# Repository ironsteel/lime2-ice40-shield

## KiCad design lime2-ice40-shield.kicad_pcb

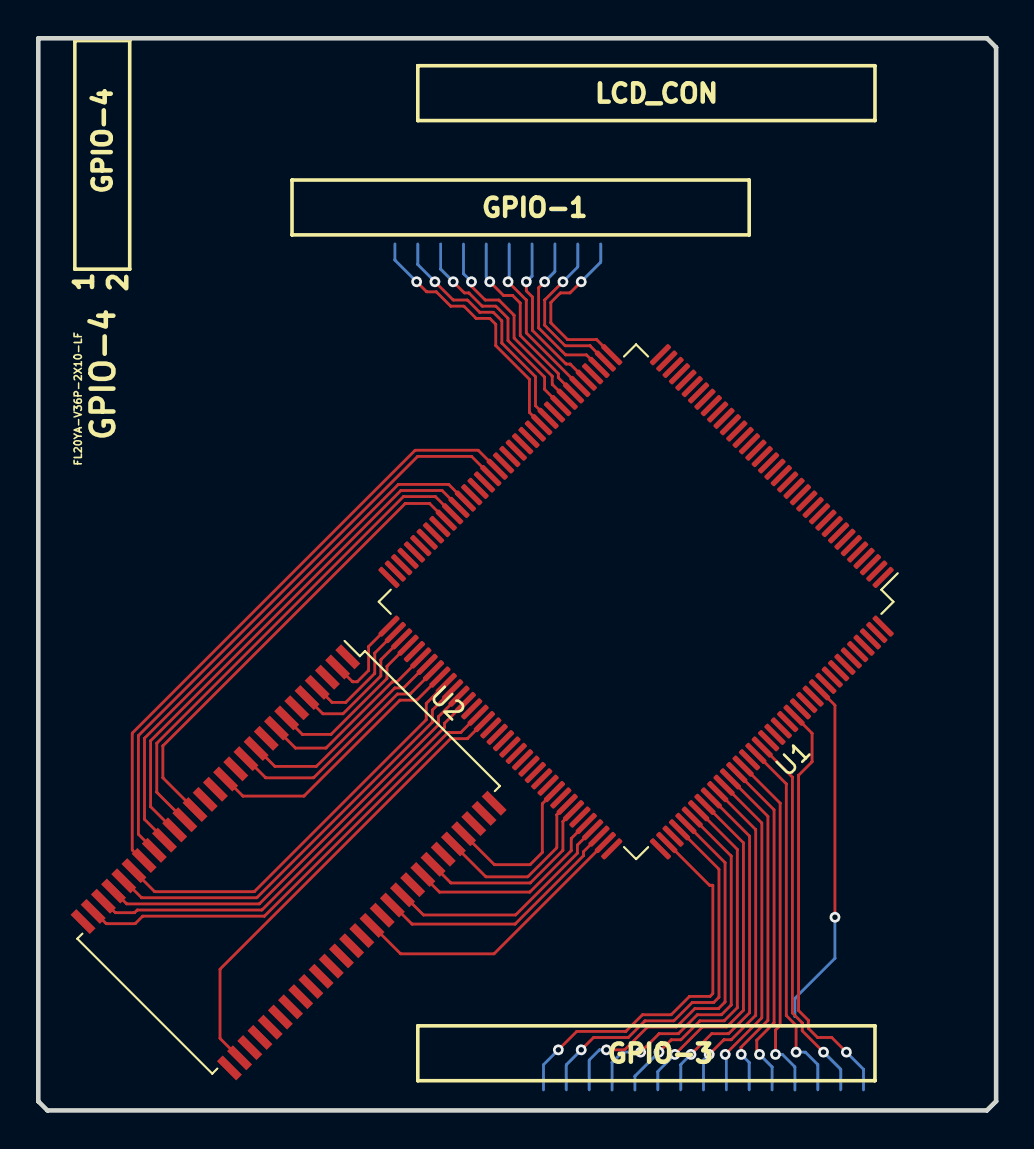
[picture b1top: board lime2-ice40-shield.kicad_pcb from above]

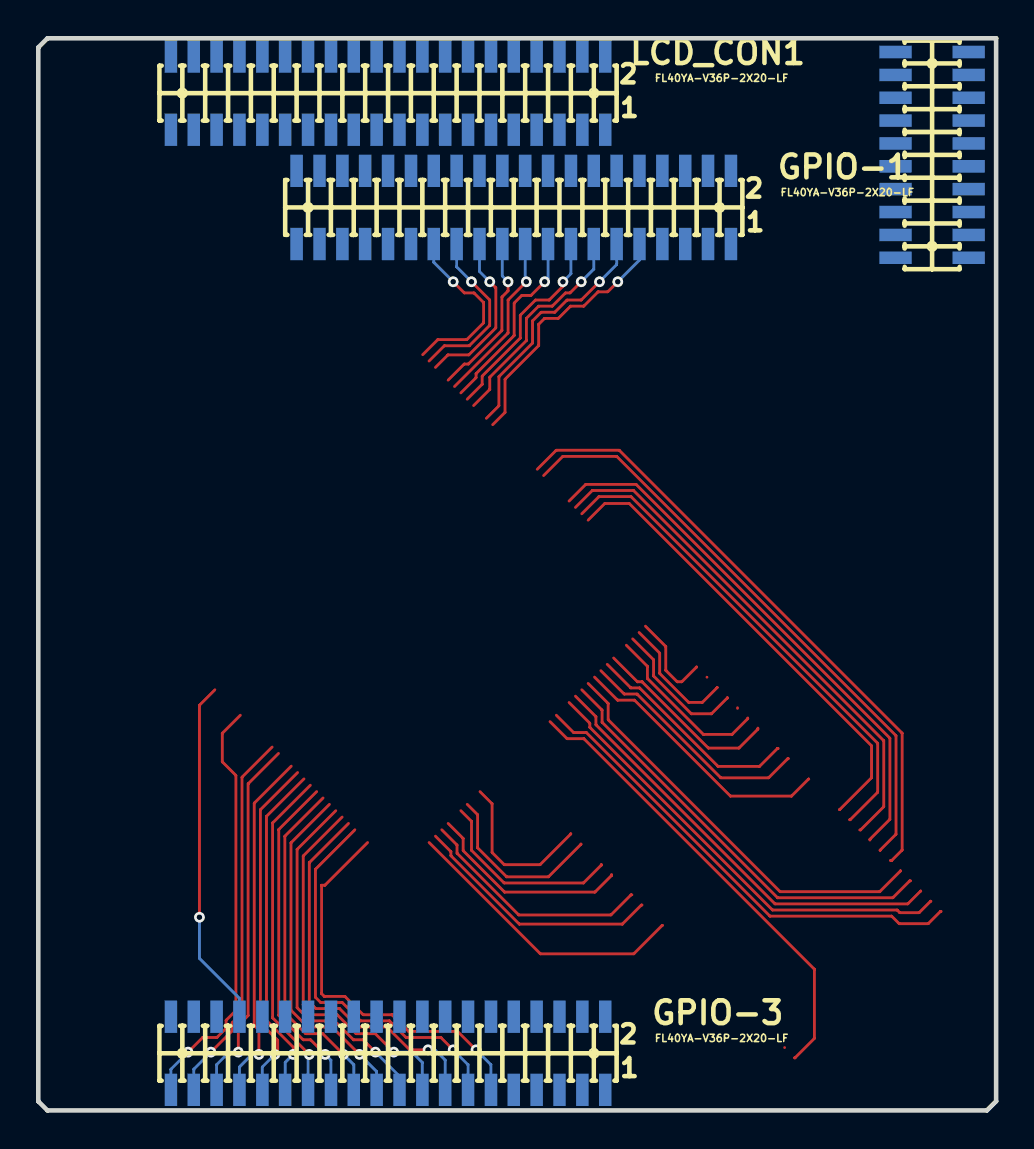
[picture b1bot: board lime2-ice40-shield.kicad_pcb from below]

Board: 2 copper layers, 53.2 x 59.6 mm, 6 parts (4 on the bottom side), 70 nets.

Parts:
GPIO-1, GPIO-3: FL40YA-V36P-2X20-LF; YA-V36P-2X20-LF
GPIO-4: FL20YA-V36P-2X10-LF; YA-V36P-2X10-LF
LCD_CON1: FL40YA-V36P-2X20-LF; YA-V36P-2X20-LF
U1: ICE40HX4K-TQ144; TQFP-144_20x20mm_P0.5mm
U2: AS4C4M16SA-6TCN; TSOP-II-54_22.2x10.16mm_P0.8mm

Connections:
+3V3: GPIO-1.3, GPIO-3.3, GPIO-4.1, LCD_CON1.3
+5V: GPIO-1.1, GPIO-3.1, LCD_CON1.1
/CSI1_D0\PG4: GPIO-1.13, U1.45
/CSI1_D1\PG5: GPIO-1.15, U1.44
/CSI1_D2\PG6: GPIO-1.17, U1.43
/CSI1_D3\PG7: GPIO-1.19, U1.42
/CSI1_D4\PG8: GPIO-1.21, U1.41
/CSI1_D5\PG9: GPIO-1.23, U1.39
/CSI1_D6\PG10: GPIO-1.25, U1.38
/CSI1_D7\PG11: GPIO-1.27, U1.37
/CSI1_D9\PH9: GPIO-3.11, U1.110
/CSI1_D10\PH10: GPIO-3.13, U1.112
/CSI1_D11\PH11: GPIO-3.15, U1.113
/CSI1_D12\PH12: GPIO-3.17, U1.114
/CSI1_D13\PH13: GPIO-3.19, U1.115
/CSI1_D14\PH14: GPIO-3.21, U1.116
/CSI1_D15\PH15: GPIO-3.23, U1.117
/CSI1_D16\PH16: GPIO-3.25, U1.118
/CSI1_D17\PH17: GPIO-3.27, U1.119
/CSI1_D18\PH18: GPIO-3.29, U1.120
/CSI1_D19\PH19: GPIO-3.31, U1.121
/CSI1_D20\PH20: GPIO-3.33, U1.122
/CSI1_D21\PH21: GPIO-3.35, U1.124
/CSI1_D22\PH22: GPIO-3.37, U1.125
/CSI1_D23\PH23: GPIO-3.39, U1.130
/CSI1_HSYNC\PG2: GPIO-1.9, U1.48
/CSI1_PCLK\PH24: GPIO-3.34, U1.134
/CSI1_VSYNC\PG3: GPIO-1.11, U1.47
/RAM_A0: U1.83, U2.23
/RAM_A1: U1.84, U2.24
/RAM_A2: U1.85, U2.25
/RAM_A3: U1.87, U2.26
/RAM_A4: U1.88, U2.29
/RAM_A5: U1.98, U2.30
/RAM_A6: U1.97, U2.31
/RAM_A7: U1.96, U2.32
/RAM_A8: U1.95, U2.33
/RAM_A9: U1.94, U2.34
/RAM_A10: U1.82, U2.22
/RAM_A11: U1.93, U2.35
/RAM_BA0: U1.56, U2.20
/RAM_BA1: U1.55, U2.21
/RAM_CAS: U1.62, U2.17
/RAM_CKE: U1.90, U2.37
/RAM_CLK: U1.91, U2.38
/RAM_CS: U1.60, U2.19
/RAM_DQ0: U1.73, U2.2
/RAM_DQ1: U1.74, U2.4
/RAM_DQ2: U1.75, U2.5
/RAM_DQ3: U1.76, U2.7
/RAM_DQ4: U1.78, U2.8
/RAM_DQ5: U1.79, U2.10
/RAM_DQ6: U1.80, U2.11
/RAM_DQ7: U1.81, U2.13
/RAM_DQ8: U1.107, U2.42
/RAM_DQ9: U1.106, U2.44
/RAM_DQ10: U1.105, U2.45
/RAM_DQ11: U1.104, U2.47
/RAM_DQ12: U1.102, U2.48
/RAM_DQ13: U1.101, U2.50
/RAM_DQ14: U1.99, U2.51
/RAM_RAS: U1.61, U2.18
/RAM_WE: U1.63, U2.16
GND: GPIO-1.2, GPIO-3.2, GPIO-4.2, LCD_CON1.2, LCD_CON1.4
unnamed: U1.6, U1.30
unnamed: U1.46, U1.57
unnamed: U1.89, U1.100
unnamed: U1.5, U1.13, U1.14, U1.59, U1.69, U1.86, U1.103, U1.132, U1.140
unnamed: U1.27, U1.40, U1.92, U1.111
unnamed: U1.123, U1.131

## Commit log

2020-09-29 Remove A20_OLIMEXINO_LIME2_SHIELD.* files
    Use footprints and symbols from lime2-ice40-shield lib files
2020-09-29 Remove .bak/,net files and add .gitignore
2020-09-30 Clean up lime2 header connections
    Left only those that will be used
2020-12-27 Add notes
2020-12-28 Initial routing of CSI1 signals
2020-12-29 Initial routing of SDRAM
